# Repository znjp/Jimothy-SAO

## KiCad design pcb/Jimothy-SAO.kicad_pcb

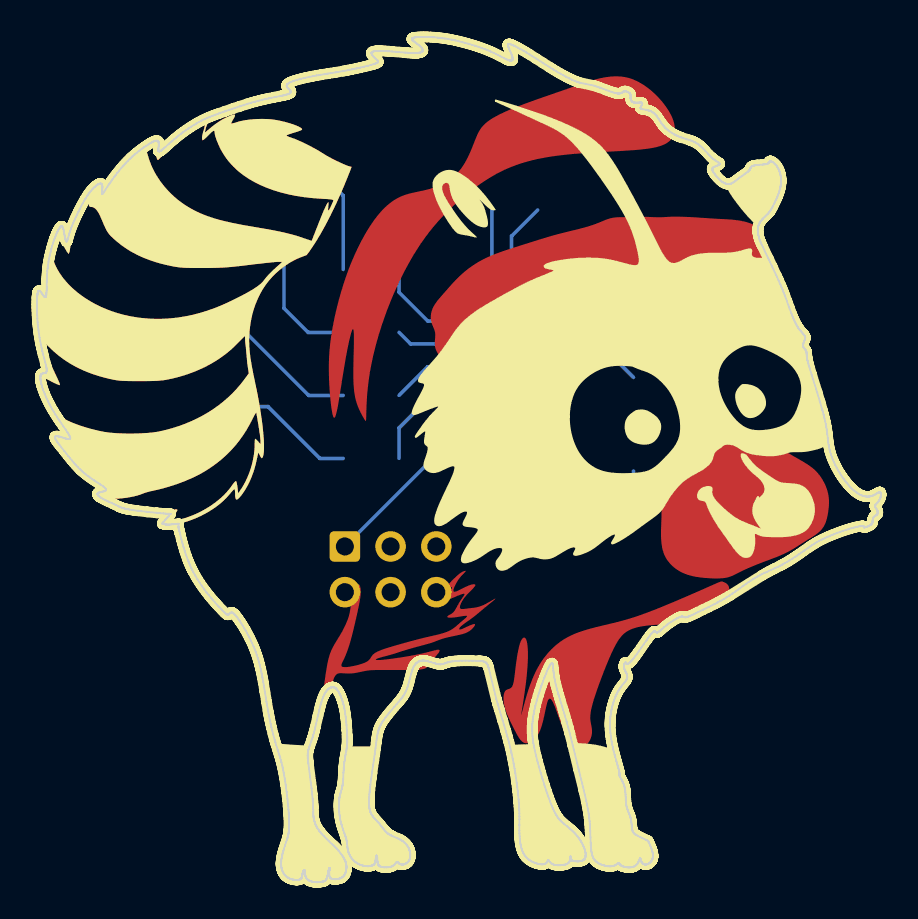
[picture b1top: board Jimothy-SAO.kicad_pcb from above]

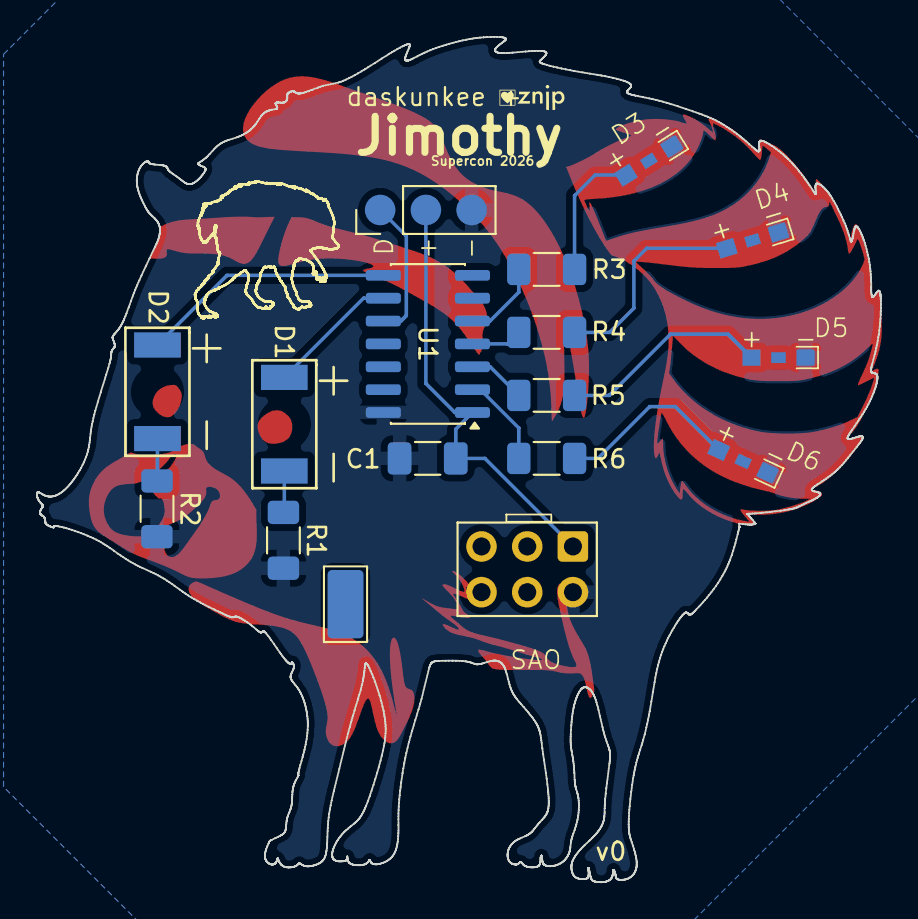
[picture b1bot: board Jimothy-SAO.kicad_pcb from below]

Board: 2 copper layers, 46.9 x 47.0 mm, 17 parts (17 on the bottom side), 15 nets.

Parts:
C1: 0.1uF; C_1206_3216Metric_Pad1.33x1.80mm_HandSolder
D1, D2: LED; SunLED 3.2x2.8mm PLCC2 SMD LED
D3, D4, D5, D6: LED; Wurth WL-SMSW Series SMT Mono-color Side view LED
R1, R2, R3, R4, R5, R6: 65R; R_1206_3216Metric_Pad1.30x1.75mm_HandSolder
SAO1: SHITTY_ADD-ON_V1.69BIS SAO
SAO_T1: SAO_Tether; TestPoint_Keystone_5019_Miniature
U1: ATtiny1624-SS; SOIC-14_3.9x8.7mm_P1.27mm
UPDI1: UPDI_Conn_01x03_Pin; UPDI_1x03_P2.54mm_SMT

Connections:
/3V3: C1.1, SAO1.1 (3.3V), U1.1 (VCC), UPDI1.2
/LEFT EYE: D1.2 (A), U1.9 (PB0)
/RIGHT EYE: D2.2 (A), U1.8 (PB1)
/RING1: R3.1, U1.5 (PA7)
/RING2: R4.1, U1.4 (PA6)
/RING3: R5.1, U1.3 (PA5)
/RING4: R6.1, U1.2 (PA4)
GND: C1.2, D3.1 (K), D4.1 (K), D5.1 (K), D6.1 (K), R1.2, R2.2, SAO1.2 (GND), U1.14 (GND), UPDI1.3
unnamed: D1.1 (K), R1.1
unnamed: D2.1 (K), R2.1
unnamed: D3.2 (A), R3.2
unnamed: D4.2 (A), R4.2
unnamed: D5.2 (A), R5.2
unnamed: D6.2 (A), R6.2
unnamed: U1.10 (~RESET/PA0), UPDI1.1

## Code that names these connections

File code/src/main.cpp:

// Jimothy SAO v0

#include <Arduino.h>

const int LEFT_EYE = PIN_PB0;
const int RIGHT_EYE = PIN_PB1;
const int RING1 = PIN_PA7;
const int RING2 = PIN_PA6;
const int RING3 = PIN_PA5;
const int RING4 = PIN_PA4;
const int RINGS[] = {RING1, RING2, RING3, RING4};
#define NUM_RINGS 4

//Stare and Blink
const unsigned long stareInterval = 5000;
unsigned long lastBlinkTime = 0; // Store the time when the eyes were last blinked
int blinkCount = 0;

void wink(){
  for(int i = 255; i > 0; i = i - 2){
    analogWrite(RIGHT_EYE, i);
    delay(2);
  }
  digitalWrite(RIGHT_EYE, LOW);
  delay(500);
  for(int i = 0; i < 255; i = i + 2){
    analogWrite(RIGHT_EYE, i);
    delay(2);
  }
}

void tailwag(){
  for(int i = 0; i < NUM_RINGS; i++){
    digitalWrite(RINGS[i], LOW);
    delay(100);
  }
  for(int i = 0; i < NUM_RINGS; i++){
    digitalWrite(RINGS[i], HIGH);
    delay(100);
  }

}

void doubleBlink(){
  digitalWrite(LEFT_EYE, LOW);
  digitalWrite(RIGHT_EYE,LOW);
  delay(100);
  digitalWrite(LEFT_EYE, HIGH);
  digitalWrite(RIGHT_EYE,HIGH);
  delay(300);
  digitalWrite(LEFT_EYE, LOW);
  digitalWrite(RIGHT_EYE,LOW);
  delay(100);
}

void awaken(){
  for(int i = 0; i < 256; i++){
    analogWrite(LEFT_EYE, i);
    analogWrite(RIGHT_EYE, i);
    delay(10);
  }
  doubleBlink();
  //wink();
  digitalWrite(LEFT_EYE,HIGH);
  digitalWrite(RIGHT_EYE,HIGH);  
  for(int i = 0; i < NUM_RINGS; i++){
    digitalWrite(RINGS[i], HIGH);
    delay(100);
  }
  delay(stareInterval);
}

void setup() {

  pinMode(LEFT_EYE, OUTPUT);
  pinMode(RIGHT_EYE, OUTPUT);
  digitalWrite(LEFT_EYE,LOW);
  digitalWrite(RIGHT_EYE,LOW);
  for(int i = 0; i < NUM_RINGS; i++){
    pinMode(i, OUTPUT);
    digitalWrite(i, LOW);
  }
  awaken();
}

void loop() {
  unsigned long currentTime = millis();

  digitalWrite(LEFT_EYE, HIGH); //Stare
  digitalWrite(RIGHT_EYE,HIGH);
  // Check if enough time has passed to blink the eyes
  if (currentTime - lastBlinkTime >= stareInterval && blinkCount < 4) {
    // Blink the eyes
    doubleBlink();
    // Update the last blink time
    lastBlinkTime = currentTime;
    blinkCount += 1;
  }
  if (currentTime - lastBlinkTime >= stareInterval && blinkCount == 4) {
    // wink
    wink();
    tailwag();
    // Update the last blink time
    lastBlinkTime = currentTime;
    blinkCount = 0;
  }

}

// [♥️]znjp
